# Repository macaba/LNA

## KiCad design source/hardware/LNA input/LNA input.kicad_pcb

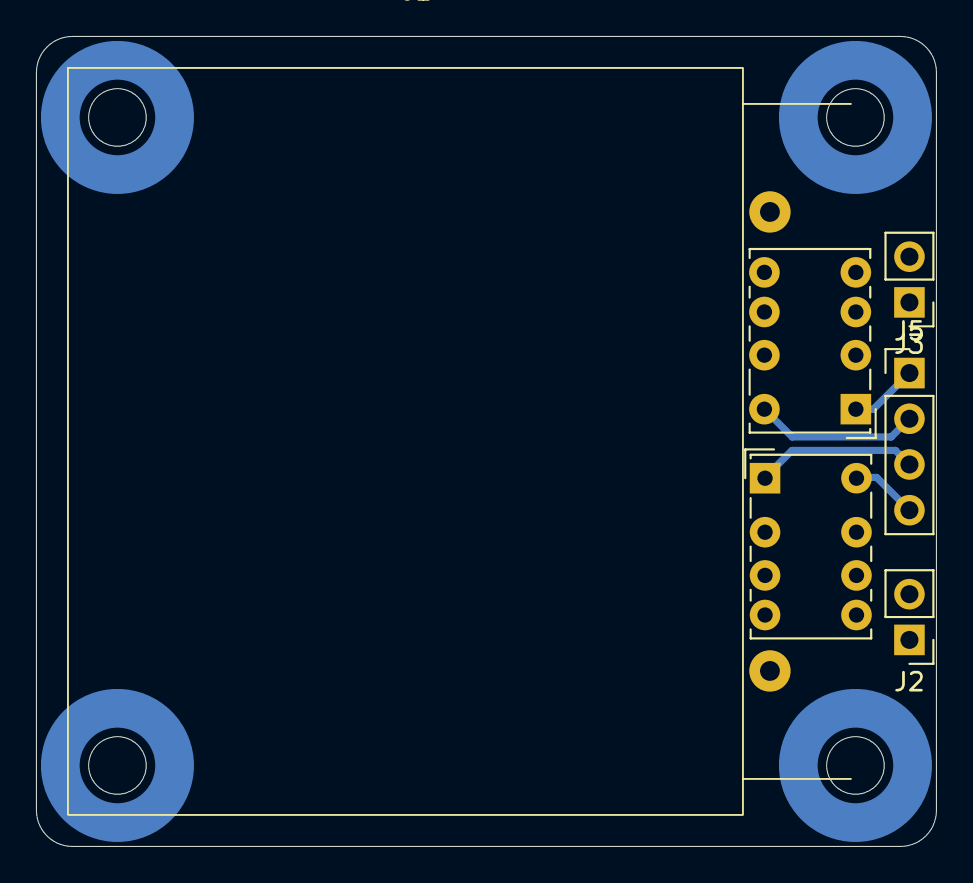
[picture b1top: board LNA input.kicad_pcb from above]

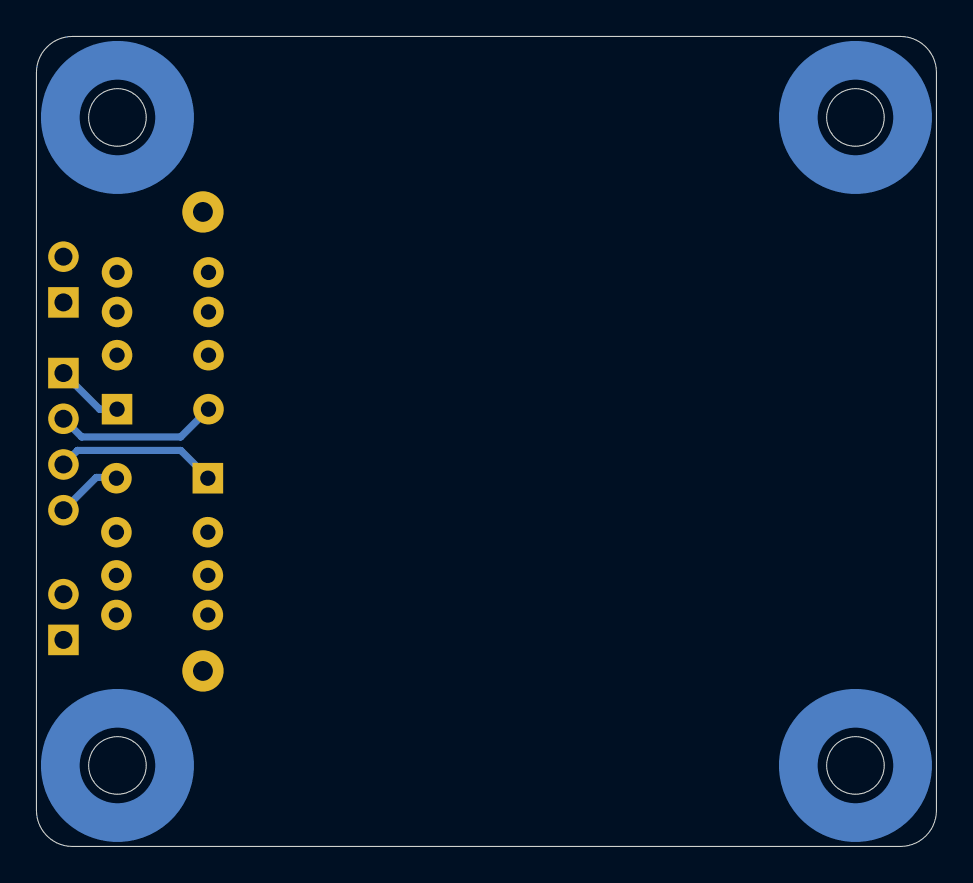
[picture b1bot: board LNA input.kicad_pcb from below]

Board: 2 copper layers, 50.0 x 45.0 mm, 10 parts (4 on the bottom side), 12 nets.

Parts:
C1: 60u; DCP4G056007GD4KSSD flat
H1, H2, H3, H4: MountingHole; 746600330
J2, J3: Conn_01x02; PinHeader_1x02_P2.54mm_Vertical
J5: Conn_01x04; PinHeader_1x04_P2.54mm_Vertical
K1, K2: G6KU-2; Relay_DPDT_Omron_G6K-2P-Y

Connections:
Cap+: C1.2, K2.4
Cap-: C1.1, K2.5
In+: J2.1, K1.4
In-: J2.2, K1.5
unnamed: J5.1, K1.1
unnamed: J5.2, K1.8
unnamed: J5.3, K2.1
unnamed: J5.4, K2.8
unnamed: K1.3, K2.3
unnamed: K2.2, K2.7
Out+: J3.2, K2.6
Out-: J3.1, K1.6

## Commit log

2023-09-19 Added simulation file
2023-09-19 Added JFE2140 files
2023-09-19 Created hardware folder, added KiCAD project files
    Project files taken from 100mm x 160mm ProtoCard template
2024-08-04 Placeholder projects
2024-08-04 added amplifier schematic
2024-08-04 Renamed project library
2024-08-04 Beginning of input board layout
